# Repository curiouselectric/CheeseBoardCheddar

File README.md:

# Cheese Board - Cheddar

This is an ESP8266 breakout board with small display, user inputs and WS2812 LEDs. 

This is designed as a low cost platform to quickly get started with projects with the ESP8266. We wanted to design something that got you up and running with your project idea quickly and easily.

The main processor is based upon the [ESP8266 system-on-chip from Espressif Systems](https://en.wikipedia.org/wiki/ESP8266).

This can be programmed via the Arduino IDE (or your favourite IDE).

This repository contains the design files, software and hardward files for this project.

We can supply this project in kit form from [The Curious Electric Company](https://www.curiouselectric.co.uk/) and Tindie.

This repository is for the hardware and instructions only. The software is available here:

https://github.com/curiouselectric/CheeseBoard_Software

## Instructions

The instructions are available in this folder as a .pdf

## PCB Overview

It is based upon the NodeMCU Amica ESP8266 module which is low-cost, easy to find and has all regulation and protection required.

There is a small I2C interfaced OLED screen on the unit for displaying data and options.

A rotary encoder is used to select various options and as the user interface.

There are five WS2812 LEDs which can be controlled via the ESP8266, along with a level shifter for good 5V operation.

A connection output is provided for HC12 wireless modules and access to a software serial output is provided through screw terminal pads.

This can be powered via USB-B or Micro-USB connector.

A screw-temrinal connector for 5V power is also supplied, if needed.

PCB design has been produced using [KiCAD](http://kicad-pcb.org/).

Hardware for the enclosure is also provided here.

### Pin Connections:

| Node MCU Conenction | Pin Number     |Function          | Arduino Alias   |
|---------------------|----------------|------------------|-----------------|
| D0                  | 30             | HC-12 SET pin    | 16              |
| D1                  | 29             | Soft Serial Tx   | 5               |
| D2                  | 28             | Soft Serial Rx   | 4               |
| D3                  | 27             | LED WS2812       | 0               |
| D4                  | 26             | I2C SCLK         | 2               |
| D5                  | 23             | I2C SDA          | 14              |
| D6                  | 22             | Enocder B        | 12              |
| D7                  | 21             | Enocder A        | 13              |
| D8                  | 20             | Encoder Switch   | 15              |
| D9                  | 19             | H/W Serial Rx    | 3               |
| D10                 | 18             | H/W Serial Tx    | 1               |
| A0                  | 1              | N/C              | A0              |

## Software Overview

This project has been designed with some interesting software to get you up and running. We wanted this project to do something useful or fun straight away. But it has been designed for hacking and for you to change, alter, adjust and play as you need.

## Hardware Overview

This kit comes with a simple enclosure to house the electronics.

This has been designed to be laser cut in 3mm acrylic. The design files are within this repository, if you would like to make your own or alter the design at all.

# To Do

* Check software in many applications
* Update instructions as required

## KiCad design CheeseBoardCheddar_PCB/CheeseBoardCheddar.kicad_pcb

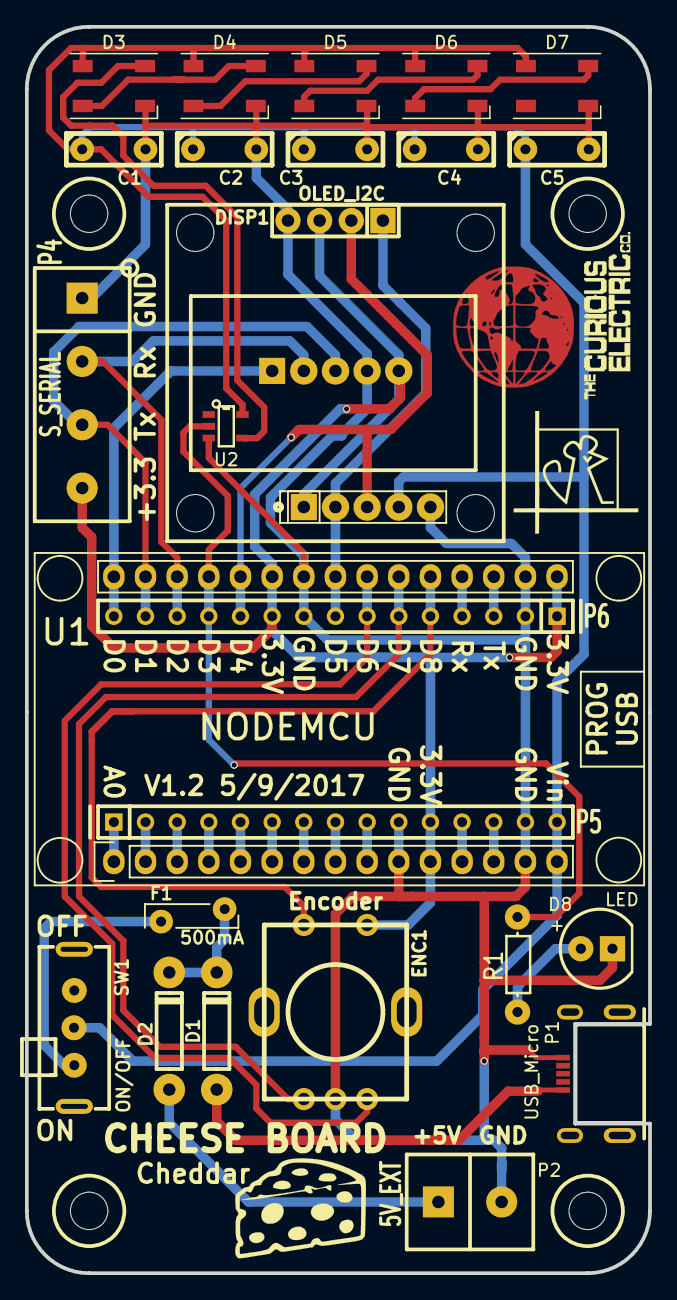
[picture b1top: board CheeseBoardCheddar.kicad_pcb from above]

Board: 2 copper layers, 50.0 x 100.0 mm, 32 parts (0 on the bottom side), 35 nets.

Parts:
C1, C2, C3, C4, C5: 100n; C1_wide_lg_pad
D1, D2: 1N5819; TH_Diode_1
D3, D4, D5, D6, D7: WS2812B_SMD; SM_WS2812B
D8: LED; TH_LED-5MM_larg_pad
DISP1: OLED_I2C; TH_OLED1306
ENC1: Encoder; TH_Encoder
F1: 500mA; TH_MC36188_FUSE
P1: USB_Micro; USB_Micro-B_MOLEX_47642-0001
P2: 5V_EXT; SIL-2_screw_terminal
P3: SERIAL_HC12; TH_SIL_5_HC12
P4: S_SERIAL; SIL-4_screw_terminals
P5: NODEMCU_1; TH_SIL-15
P6: NODEMCU_2; TH_SIL-15
P7: PCB; PCB_50x100mm_RJWIFI
P8: LOGO_MOUSE; mouse10x10
P10: LOGO1; CEC_Globe_10mm_FCU
P11: LOGO2; TCEC_Words_13mm
P13: LOGO_CHEESE; CheeseWedge8mm
P14: I2C_EXT; SIL-5_large_pads_marker
R1: 330; TH_Resistor_1
SW1: ON/OFF; SW_SPDT_R_Angle_ALIEX
U1: NODEMCU; NodeMCU_Amica_R2_FSILK
U2: 74LVC1G17; SM_SOT-23-5

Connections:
+3V3: DISP1.3, ENC1.2, P3.5, P4.4, P5.11, P6.1, P6.10, P14.1, U1.11, U1.16, U1.25
/5V_PWR: C1.1, C2.1, C3.1, C4.1, C5.1, D3.1, D4.1, D5.1, D6.1, D7.1, P5.15, P14.4, SW1.2, U1.15, U2.5
/ENC_A: ENC1.A, P6.6, U1.21
/ENC_B: ENC1.B, P6.7, U1.22
/HC12_SET: P3.1, P6.15, U1.30
/LED_WS2811: P6.12, R1.1, U1.27, U2.2
/Rx: P6.4, U1.19
/SCL: DISP1.2, P6.11, P14.3, U1.26
/SDA: DISP1.1, P6.8, P14.2, U1.23
/SOFT_Rx: P3.2, P4.2, P6.13, U1.28
/SOFT_Tx: P3.3, P4.3, P6.14, U1.29
/SW_ENC: ENC1.1, P6.5, U1.20
/Tx: P6.3, U1.18
GND: C1.2, C2.2, C3.2, C4.2, C5.2, D3.3, D4.3, D5.3, D6.3, D7.3, D8.1, DISP1.4, ENC1.C, P1.5, P2.2, P3.4, P4.1, P5.10, P5.14, P6.2, P6.9, P14.5, U1.10, U1.14, U1.17, U1.24, U2.3
unnamed: D1.1, D2.1, F1.1
unnamed: D1.2, P1.1
unnamed: D2.2, P2.1
unnamed: D3.2, D4.4
unnamed: D3.4, U2.4
unnamed: D4.2, D5.4
unnamed: D5.2, D6.4
unnamed: D6.2, D7.4
unnamed: D8.2, R1.2
unnamed: F1.2, SW1.1
unnamed: P5.1, U1.1
unnamed: P5.2, U1.2
unnamed: P5.3, U1.3
unnamed: P5.4, U1.4
unnamed: P5.5, U1.5
unnamed: P5.6, U1.6
unnamed: P5.7, U1.7
unnamed: P5.8, U1.8
unnamed: P5.9, U1.9
unnamed: P5.12, U1.12
unnamed: P5.13, U1.13

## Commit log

2017-08-03 Initial commit of basic PCB files
2017-08-03 Update of Readme and PCB changed
2017-08-07 PCB changes
2017-08-08 Small PCB changes
2017-08-09 PCB initial wiring. Cost and Parts info done
2017-08-11 Full review of boards - needs NAME still!
2017-09-05 Updated PCB with name
2017-09-06 Update with new name
2017-09-06 Slight update of silkscreen on PCB
2017-09-24 Updated PCB with Encoder switch sorted
2017-09-24 Instruction Template added
2017-10-07 Updated enclosure design
2017-11-05 Updated enclsoure
2017-11-24 UpdatedI nstructions
2017-12-02 Added I2C bus to PCB
2017-12-24 Update of instructions
2018-02-17 Updated instructions and .dxf files
2018-02-24 Added Software from Mouse
    Added software
2018-02-24 Updated Instructions
2018-02-28 Removed software from this repository
    Creating hardware and software repositories
2018-09-16 Small Changes
